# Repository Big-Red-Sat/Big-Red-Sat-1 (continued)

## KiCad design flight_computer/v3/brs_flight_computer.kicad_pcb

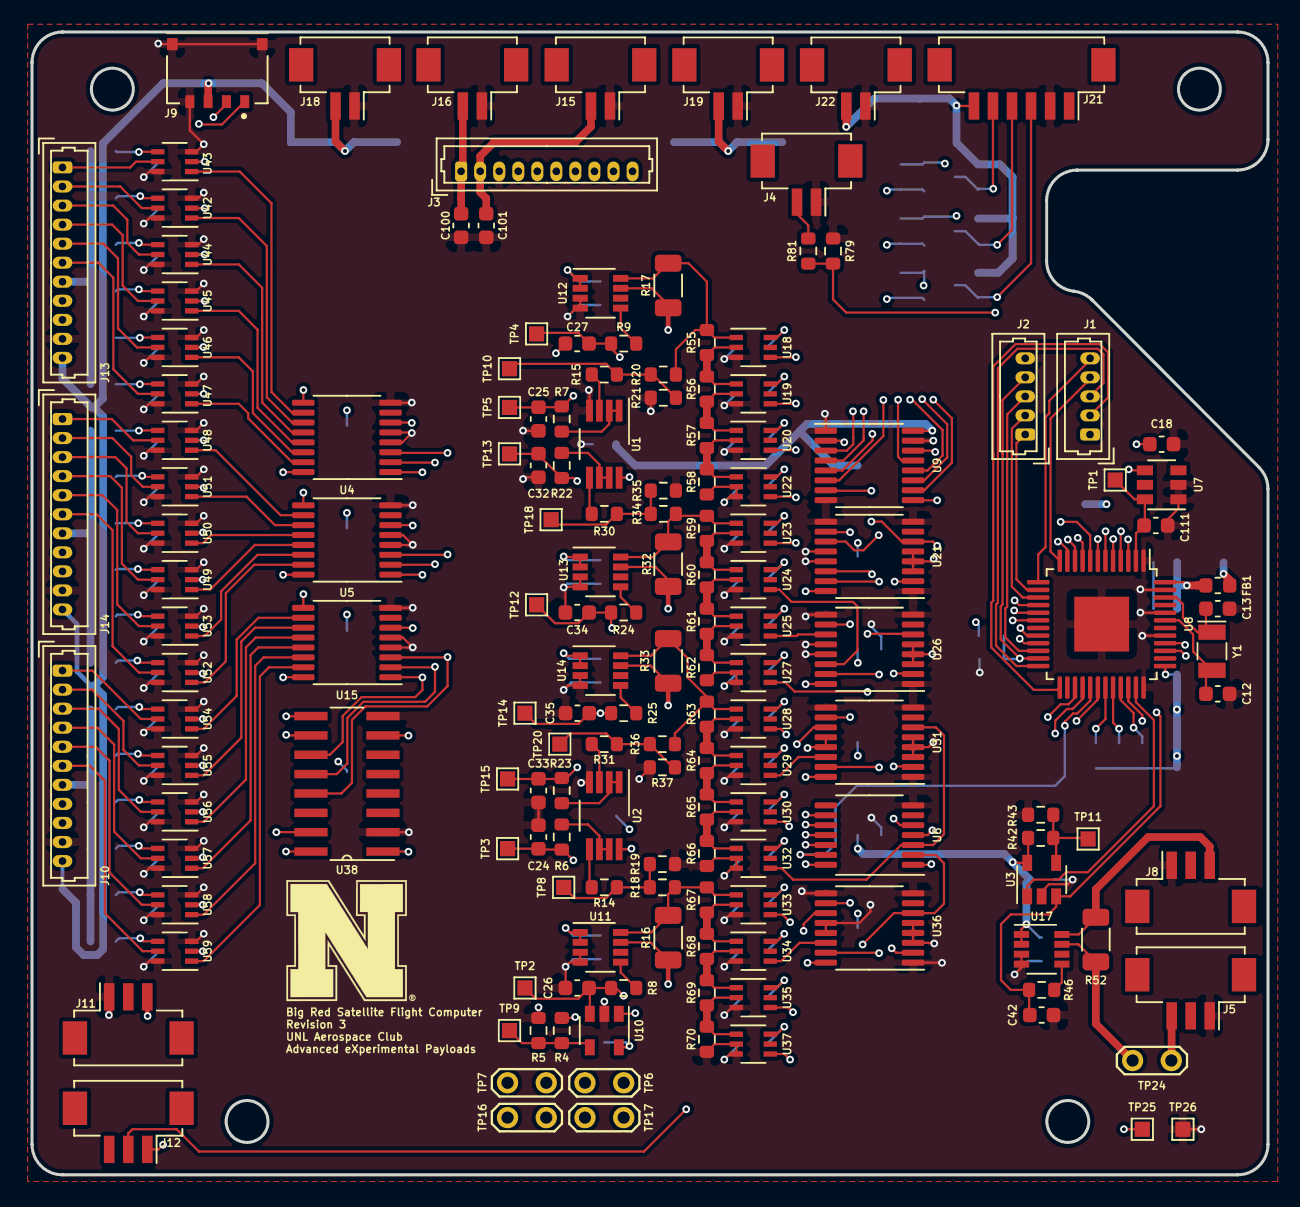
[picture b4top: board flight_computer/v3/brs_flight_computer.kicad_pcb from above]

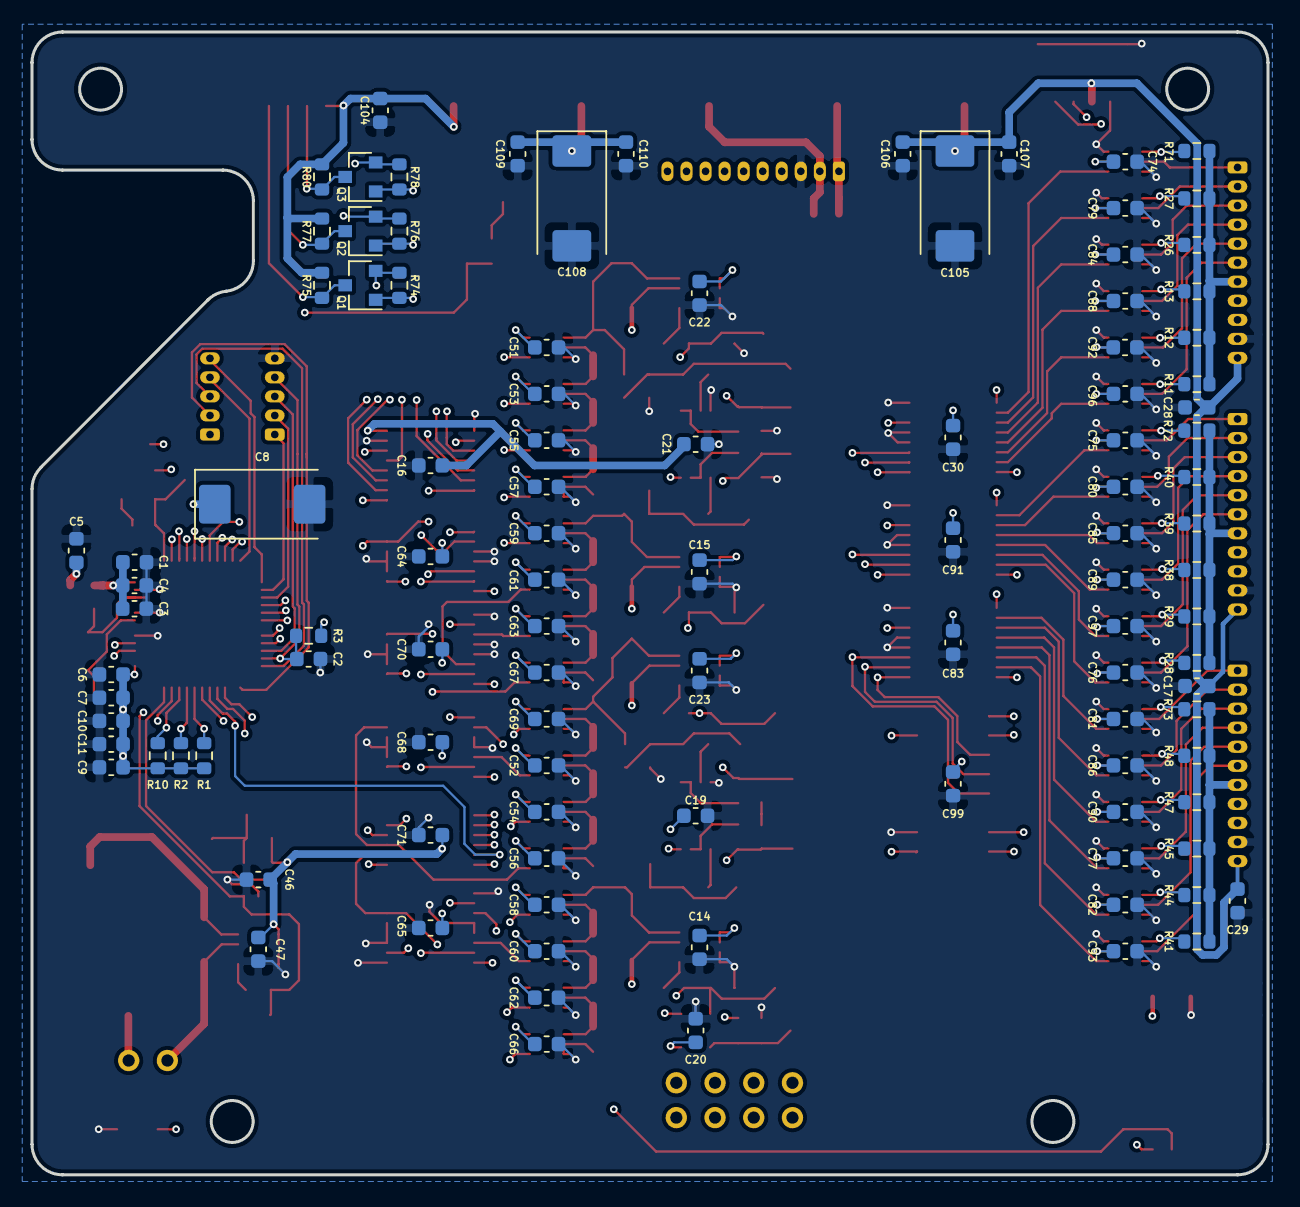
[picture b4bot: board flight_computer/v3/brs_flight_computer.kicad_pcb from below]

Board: 4 copper layers, 81.1 x 75.0 mm, 265 parts (105 on the bottom side), 177 nets.

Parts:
C1, C10, C100, C106, C109: 10u; C_0603_1608Metric
C2, C4, C5, C6, C9, C11, C14, C15, C16, C17, C18, C19, C20, C21, C22, C23, C28, C29, C30, C51, C52, C53, C54, C55, C56, C57, C58, C59, C60, C61, C62, C63, C64, C65, C66, C67, C68, C69, C70, C71, C74, C75, C76, C77, C79, C80, C81, C82, C83, C84, C85, C86, C88, C89, C90, C91, C92, C93, C96, C97, C99, C101, C104, C107, C110, C111: 0.1u; C_0603_1608Metric
C3, C7, C46, C47: 1u; C_0603_1608Metric
C8, C105, C108: 47u; CP_EIA-7343-43_Kemet-X
C12, C13: 10p; C_0603_1608Metric
C24, C25, C26, C27, C32, C33, C34, C35, C42: 10n; C_0603_1608Metric
FB1: Ferrite_Bead_Small; L_0603_1608Metric
J1, J2: Conn_01x05_Male; Molex_PicoBlade_53047-0510_1x05_P1.25mm_Vertical
J3: Conn_01x10_Male; Molex_PicoBlade_53047-1010_1x10_P1.25mm_Vertical
J4: BUSS; Hirose_DF13C_CL535-0402-2-51_1x02-1MP_P1.25mm_Vertical
J5: Panel 3; Hirose_DF13C_CL535-0403-5-51_1x03-1MP_P1.25mm_Vertical
J8: Conn_01x03_Male; Hirose_DF13C_CL535-0403-5-51_1x03-1MP_P1.25mm_Vertical
J9: 0781710004; MOLEX_0781710004
J10: Perovskite 3; Molex_PicoBlade_53047-1110_1x11_P1.25mm_Vertical
J11: GaAs Panel; Hirose_DF13C_CL535-0403-5-51_1x03-1MP_P1.25mm_Vertical
J12: GaAs Temperature; Hirose_DF13C_CL535-0403-5-51_1x03-1MP_P1.25mm_Vertical
J13: Perovskite 1; Molex_PicoBlade_53047-1110_1x11_P1.25mm_Vertical
J14: Perovskite 2; Molex_PicoBlade_53047-1110_1x11_P1.25mm_Vertical
J15, J16, J18, J19, J22: Power; Hirose_DF13C_CL535-0402-2-51_1x02-1MP_P1.25mm_Vertical
J21: EPS Serial; Hirose_DF13C_CL535-0406-3-51_1x06-1MP_P1.25mm_Vertical
Q1, Q2, Q3: BSS138; SOT-23
R1, R2, R10: 4k7; R_0603_1608Metric
R3, R74, R75, R76, R77, R78, R80: 10k; R_0603_1608Metric
R4, R5, R6, R7, R8, R9, R14, R15, R22, R23, R24, R25, R30, R31, R42, R43, R46: 470; R_0603_1608Metric
R11, R12, R13, R26, R27, R28, R29, R38, R39, R40, R41, R44, R45, R47, R48, R71, R72, R73: 400; R_0603_1608Metric
R16, R17, R32, R33, R52: 510m; R_1206_3216Metric
R18, R81: 3M; R_0603_1608Metric
R19, R20, R21, R34, R35, R36, R37, R55, R59, R63, R67, R79: 1M; R_0603_1608Metric
R56, R60, R64, R68: 430; R_0603_1608Metric
R57, R61, R65, R69: 270; R_0603_1608Metric
R58, R62, R66, R70: 120; R_0603_1608Metric
TP1: VREF; TestPoint_Pad_1.0x1.0mm
TP2, TP4, TP11, TP12, TP14: I; TestPoint_Pad_1.0x1.0mm
TP3, TP5, TP13, TP15: V; TestPoint_Pad_1.0x1.0mm
TP6, TP7, TP16, TP17, TP24: Current Test; TestPoint_2Pads_Pitch2.54mm_Drill0.8mm
TP8, TP9, TP10, TP18, TP20: Voltage Test+; TestPoint_Pad_1.0x1.0mm
TP25: 3V3; TestPoint_Pad_1.0x1.0mm
TP26: GND; TestPoint_Pad_1.0x1.0mm
U1, U2: OPA2387; VSSOP-8_3.0x3.0mm_P0.65mm
U3, U10: TLV7031DBV; SOT-23-5
U4, U5, U15: 74HC237; TSSOP-16_4.4x5mm_P0.65mm
U6: 4012; TSSOP-14_4.4x5mm_P0.65mm
U7: LT6654AHS6-3.3; SOT-23-6
U8: MSP430FR5969IRGZR; LQFP-48-1EP_7x7mm_P0.5mm_EP3.6x3.6mm
U9: SN74CBT3253; TSSOP-16_4.4x5mm_P0.65mm
U11, U12, U13, U14, U17: INA190A4IDDFR
U18, U19, U20, U22, U23, U24, U25, U27, U28, U29, U30, U32, U33, U34, U35, U37: ADG841YKSZ-500RL7
U21, U26, U31, U36: CD4516B_PW_16; TSSOP-16_4.4x5mm_P0.65mm
U38: CD4518BM96
U42, U43, U44, U45, U46, U47, U48, U49, U50, U51, U52, U53, U54, U55, U56, U57, U58, U59: ADG839YKSZ-REEL7
Y1: CM8V-T1A; Crystal_SMD_MicroCrystal_CC7V-T1A-2Pin_3.2x1.5mm

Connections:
+3V3: C5.1, C6.1, C7.1, C8.1, C9.2, C10.2, C11.2, C14.1, C16.1, C18.2, C20.1, C21.1, C30.1, C58.1, C60.1, C62.1, C65.1, C66.1, C74.1, C75.1, C76.1, C77.1, C79.1, C80.1, C81.1, C82.1, C83.1, C84.1, C85.1, C86.1, C88.1, C89.1, C90.1, C91.1, C92.1, C93.1, C96.1, C97.1, C99.1, C108.1, C109.1, C110.1, FB1.1, J1.1, J12.1, J19.2, Q1.1, Q2.1, Q3.1, R1.2, R2.2, R3.2, R4.1, R10.2, R74.2, R76.2, R78.2, TP25.1, U2.8, U4.6, U4.16, U5.6, U5.16, U6.12, U7.4, U8.37, U9.16, U10.5, U11.1, U11.2, U15.6, U15.16, U33.6, U34.6, U35.6, U36.16, U37.6, U38.1, U38.7, U38.10, U38.16, U42.2, U43.2, U44.2, U45.2, U46.2, U47.2, U48.2, U49.2, U50.2, U51.2, U52.2, U53.2, U54.2, U55.2, U56.2, U57.2, U58.2, U59.2
+5V: C104.1, J21.6, J22.2, R75.2, R77.2, R80.2
/Curve Tracer/GAAS_LADDER: R16.1, R18.2, R67.2, U11.8, U33.1
/Curve Tracer/GAAS_ON: U8.28, U10.1
/Curve Tracer/GAAS_POS: J11.3, TP6.1
/Curve Tracer/P_1_LADDER: R17.2, R20.2, R55.2, U12.8, U18.1
/Curve Tracer/P_2_LADDER: R32.1, R34.2, R59.2, U13.8, U23.1
/Curve Tracer/P_3_LADDER: R33.2, R36.2, R63.2, U14.8, U28.1
/Curve Tracer/READ_CURRENT: U8.10, U9.7
/Curve Tracer/READ_VOLTAGE: U8.11, U9.9
/Curve Tracer/S0_CT: U8.8, U9.14
/Curve Tracer/S1_CT: U8.9, U9.2
/EPS Connections/BUSY: Q1.2, R74.1, U8.34
/EPS Connections/READ_BUSS: R79.1, R81.1, U8.16
/EPS Connections/RX: Q3.2, R78.1, U8.21
/EPS Connections/TX: Q2.2, R76.1, U8.20
/Ground Switcher/GAAS_TEMP: J12.2, R10.1, U8.33
/Ground Switcher/MUX_CLOCK: U8.30, U38.9
/Ground Switcher/MUX_GOOD: U6.13, U8.29
/Ground Switcher/MUX_RESET: U8.39, U38.15
/Ground Switcher/SCL: J3.4, J9.2, J10.9, J13.9, J14.9, R2.1, U8.32
/Ground Switcher/SDA: J3.5, J9.1, J10.8, J13.8, J14.8, R1.1, U8.31
/Microcontroller/CT_GOOD: U6.1, U8.27
/Microcontroller/LADDER_CLOCK: U8.17, U21.15, U26.15, U31.15, U36.15
/Microcontroller/MAG_INT: J3.6, U8.7
/Microcontroller/NC_V: J3.10, U8.3
/Microcontroller/NO_V: J3.9, U8.4
/Microcontroller/PANEL_3_CURRENT_V: C42.1, R46.1, U3.3, U8.40
/Microcontroller/SET: J3.7, U8.6
/Microcontroller/TRACE_DIR: U8.18, U21.10, U26.10, U31.10, U36.10
/Microcontroller/UNSET: J3.8, U8.5
/Passive ADCS/PANEL_3_CURRENT: U3.1, U8.35
GAAS_CURRENT: C26.1, R8.1, TP2.1, U9.6, U10.3
GAAS_VOLTAGE: C24.1, R6.1, TP3.1, U9.10
GND: C1.2, C2.1, C3.2, C4.2, C5.2, C6.2, C7.2, C8.2, C9.1, C10.1, C11.1, C12.2, C13.1, C14.2, C15.2, C16.2, C17.2, C18.1, C19.2, C20.2, C21.2, C22.2, C23.2, C24.2, C25.2, C26.2, C27.2, C28.2, C29.2, C30.2, C32.2, C33.2, C34.2, C35.2, C42.2, C46.2, C47.2, C51.2, C52.2, C53.2, C54.2, C55.2, C56.2, C57.2, C58.2, C59.2, C60.2, C61.2, C62.2, C63.2, C64.2, C65.2, C66.2, C67.2, C68.2, C69.2, C70.2, C71.2, C74.2, C75.2, C76.2, C77.2, C79.2, C80.2, C81.2, C82.2, C83.2, C84.2, C85.2, C86.2, C88.2, C89.2, C90.2, C91.2, C92.2, C93.2, C96.2, C97.2, C99.2, C100.2, C101.2, C104.2, C105.2, C106.2, C107.2, C108.2, C109.2, C110.2, C111.1, J2.5, J3.3, J4.1, J5.1, J8.1, J9.4, J9.S1, J9.S2, J10.10, J11.1, J13.10, J14.10, J15.1, J16.1, J18.1, J19.1, J21.2, J22.1, R5.2, R19.1, R21.1, R35.1, R37.1, R43.2, R58.1, R62.1, R66.1, R70.1, R79.2, TP26.1, U1.4, U2.4, U3.2, U4.4, U4.5, U4.8, U5.4, U5.5, U5.8, U6.7, U7.1, U7.2, U8.1, U8.36, U8.41, U8.44, U8.47, U8.49, U9.1, U9.8, U9.15, U10.2, U11.3, U11.4, U12.3, U12.4, U13.3, U13.4, U14.3, U14.4, U15.4, U15.5, U15.8, U17.3, U17.4, U18.3, U19.3, U20.3, U21.1, U21.3, U21.4, U21.5, U21.8, U21.9, U21.12, U21.13, U22.2, U22.3, U23.3, U24.3, U25.3, U26.1, U26.3, U26.4, U26.5, U26.8, U26.9, U26.12, U26.13, U27.2, U27.3, U28.3, U29.3, U30.3, U31.1, U31.3, U31.4, U31.5, U31.8, U31.9, U31.12, U31.13, U32.2, U32.3, U33.3, U34.3, U35.3, U36.1, U36.3, U36.4, U36.5, U36.8, U36.9, U36.12, U36.13, U37.2, U37.3, U38.2, U38.8, U42.3, U42.6, U43.3, U43.6, U44.3, U44.6, U45.3, U45.6, U46.3, U46.6, U47.3, U47.6, U48.3, U48.6, U49.3, U49.6, U50.3, U50.6, U51.3, U51.6, U52.3, U52.6, U53.3, U53.6, U54.3, U54.6, U55.3, U55.6, U56.3, U56.6, U57.3, U57.6, U58.3, U58.6, U59.3, U59.6
unnamed: C12.1, U8.43, Y1.2
unnamed: C13.2, U8.46, Y1.1
unnamed: C111.2, TP1.1, U7.6, U8.2
unnamed: J4.2, R81.2
unnamed: J5.3, TP24.1
unnamed: J8.3, R52.1, U17.8
unnamed: J21.3, Q1.3, R75.1
unnamed: J21.4, Q2.3, R77.1
unnamed: J21.5, Q3.3, R80.1
unnamed: R4.2, R5.1, TP9.1, U10.4
unnamed: R6.2, U2.6, U2.7
unnamed: R7.2, U1.1, U1.2
unnamed: R8.2, U11.5
unnamed: R9.2, U12.5
unnamed: R11.2, U47.4
unnamed: R12.2, U46.4
unnamed: R13.2, U45.4
unnamed: R14.1, U2.5
unnamed: R14.2, R18.1, R19.2, TP8.1
unnamed: R15.1, U1.3
unnamed: R15.2, R20.1, R21.2, TP10.1
unnamed: R16.2, TP6.2, U11.7
unnamed: R17.1, TP7.2, U12.7
unnamed: R22.2, U1.6, U1.7
unnamed: R23.2, U2.1, U2.2
unnamed: R24.2, U13.5
unnamed: R25.2, U14.5
unnamed: R26.2, U44.4
unnamed: R27.2, U42.4
unnamed: R28.2, U52.4
unnamed: R29.2, U53.4
unnamed: R30.1, U1.5
unnamed: R30.2, R34.1, R35.2, TP18.1
unnamed: R31.1, U2.3
unnamed: R31.2, R36.1, R37.2, TP20.1
unnamed: R32.2, TP16.2, U13.7
unnamed: R33.1, TP17.2, U14.7
unnamed: R38.2, U49.4
unnamed: R39.2, U50.4
unnamed: R40.2, U51.4
unnamed: R41.2, U59.4
unnamed: R42.2, R43.1, TP11.1, U3.4
unnamed: R44.2, U58.4
unnamed: R45.2, U57.4
unnamed: R46.2, U17.5
unnamed: R47.2, U56.4
unnamed: R48.2, U55.4
unnamed: R52.2, TP24.2, U17.7
unnamed: R55.1, R56.2, U18.2, U19.1
unnamed: R56.1, R57.2, U19.2, U20.1
unnamed: R57.1, R58.2, U20.2, U22.1
unnamed: R59.1, R60.2, U23.2, U24.1
unnamed: R60.1, R61.2, U24.2, U25.1
unnamed: R61.1, R62.2, U25.2, U27.1
unnamed: R63.1, R64.2, U28.2, U29.1
unnamed: R64.1, R65.2, U29.2, U30.1
unnamed: R65.1, R66.2, U30.2, U32.1
unnamed: R67.1, R68.2, U33.2, U34.1
unnamed: R68.1, R69.2, U34.2, U35.1
unnamed: R69.1, R70.2, U35.2, U37.1
unnamed: R71.2, U43.4
unnamed: R72.2, U48.4
unnamed: R73.2, U54.4
unnamed: U4.9, U6.9
unnamed: U4.10, U43.1
unnamed: U4.11, U42.1
unnamed: U4.12, U44.1
unnamed: U4.13, U45.1
unnamed: U4.14, U46.1
unnamed: U4.15, U47.1
unnamed: U5.9, U6.10
unnamed: U5.11, U51.1
unnamed: U5.12, U50.1
unnamed: U5.14, U53.1
unnamed: U5.15, U52.1
unnamed: U4.1, U5.1, U15.1, U38.11
unnamed: U4.2, U5.2, U15.2, U38.12
unnamed: U4.3, U5.3, U15.3, U38.13
unnamed: U6.11, U15.9
unnamed: U15.10, U54.1
unnamed: U15.11, U55.1
unnamed: U15.12, U56.1
unnamed: U15.13, U57.1
unnamed: U15.14, U58.1
unnamed: U15.15, U59.1
unnamed: U18.4, U21.2
unnamed: U19.4, U21.14
unnamed: U20.4, U21.11
unnamed: U6.5, U21.6, U22.4
unnamed: U23.4, U26.2
unnamed: U24.4, U26.14
unnamed: U25.4, U26.11
unnamed: U6.4, U26.6, U27.4
unnamed: U28.4, U31.2
unnamed: U29.4, U31.14
unnamed: U30.4, U31.11
unnamed: U6.3, U31.6, U32.4
unnamed: U33.4, U36.2
unnamed: U34.4, U36.14
unnamed: U35.4, U36.11
unnamed: U6.2, U36.6, U37.4
unnamed: U5.10, U48.1
unnamed: U5.13, U49.1
P1_CP: J13.7, R11.1, R12.1, R13.1, R26.1, R27.1, R71.1, TP7.1
P1_P1: J13.6, U47.5
P1_P2: J13.5, U46.5
P1_P3: J13.4, U45.5
P1_P4: J13.1, U43.5
P1_P5: J13.2, U42.5
P1_P6: J13.3, U44.5
P2_CP: J14.7, R28.1, R29.1, R38.1, R39.1, R40.1, R72.1, TP16.1
P2_P1: J14.6, U52.5
P2_P2: J14.5, U53.5
P2_P3: J14.4, U49.5
P2_P4: J14.1, U48.5
P2_P5: J14.2, U51.5
P2_P6: J14.3, U50.5
P3_CP: J10.7, R41.1, R44.1, R45.1, R47.1, R48.1, R73.1, TP17.1
P3_P1: J10.6, U59.5
P3_P2: J10.5, U58.5
P3_P3: J10.4, U57.5
P3_P4: J10.1, U54.5
P3_P5: J10.2, U55.5
P3_P6: J10.3, U56.5
PAYLOAD_RST: C2.2, J2.4, R3.1, U8.23
P_1_CURRENT: C27.1, R9.1, TP4.1, U9.3
P_1_VOLTAGE: C25.1, R7.1, TP5.1, U9.13
P_2_CURRENT: C34.1, R24.1, TP12.1, U9.4
P_2_VOLTAGE: C32.1, R22.1, TP13.1, U9.12
P_3_CURRENT: C35.1, R25.1, TP14.1, U9.5
P_3_VOLTAGE: C33.1, R23.1, TP15.1, U9.11
RX_IN: J1.2, U8.25
TCK: J2.2, U8.15
TDI: J1.5, U8.13
TDO: J1.4, U8.12
TEST: J2.3, U8.22
TMS: J2.1, U8.14
TX_OUT: J1.3, U8.24
VAA: C1.1, C3.1, C4.1, FB1.2, U8.48
VBUS: C15.1, C17.1, C19.1, C22.1, C23.1, C28.1, C29.1, C46.1, C47.1, C51.1, C52.1, C53.1, C54.1, C55.1, C56.1, C57.1, C59.1, C61.1, C63.1, C64.1, C67.1, C68.1, C69.1, C70.1, C71.1, C105.1, C106.1, C107.1, J9.3, J10.11, J13.11, J14.11, J18.2, R42.1, U1.8, U3.5, U6.14, U12.1, U12.2, U13.1, U13.2, U14.1, U14.2, U17.1, U17.2, U18.6, U19.6, U20.6, U21.16, U22.6, U23.6, U24.6, U25.6, U26.16, U27.6, U28.6, U29.6, U30.6, U31.16, U32.6
VDDF: C100.1, J3.1, J16.2
VPP: C101.1, J3.2, J15.2

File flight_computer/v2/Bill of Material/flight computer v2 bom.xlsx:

Ref | Quantity | Value | Footprint | Rating | Vendor
C1, C10, C100, C106, C109, | 5 | 10u | Capacitor_SMD:C_0603_1608Metric | AEC-Q200 | https://www.digikey.com/en/products/detail/kyocera-avx/KAM15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
C2, C4, C5, C6, C9, C11, C14, C15, C16, C17, C18, C19, C20, C21, C22, C23, C28,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 | 66 | 0.1u | Capacitor_SMD:C_0603_1608Metric | COTS | https://www.digikey.com/en/products/detail/kemet/C0603T104K5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
C3, C7, C46, C47, C48, | 5 | 1u | Capacitor_SMD:C_0603_1608Metric | AEC-Q200 | https://www.digikey.com/en/products/detail/tdk-corporation/C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
C8, C105, C108, | 3 | 47u | Capacitor_Tantalum_SMD:CP_EIA-7343-43_Kemet-X | COTS | https://www.digikey.com/en/products/detail/kemet/T541X227M01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
C12, C13, | 2 | 10p | Capacitor_SMD:C_0603_1608Metric | COTS | https://www.digikey.com/en/products/detail/kemet/C0603T100J5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
C24, C25, C26, C27, C32, C33, C34, C35, C42, | 9 | 10n | Capacitor_SMD:C_0603_1608Metric | COTS | https://www.digikey.com/en/products/detail/kemet/C0603T103K5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
FB1, | 1 | Ferrite_Bead_Small | Inductor_SMD:L_0603_1608Metric | AEC-Q200 | https://www.digikey.com/en/products/detail/tdk-corporation/M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
R1, R2, | 2 | 4k7 | Resistor_SMD:R_0603_1608Metric | AEC-Q200 | https://www.digikey.com/en/products/detail/vishay-dale/TNPW0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
R3, R71, R72, R73, R74, R75, R76, R77, R78, R80, | 10 | 10k | Resistor_SMD:R_0603_1608Metric | "Military" | https://www.digikey.com/en/products/detail/vishay-dale/TNPW0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
R4, R5, R6, R7, R8, R9, R14, R15, R22, R23, R24, R25, R30, R31, R42, R43, R46, | 17 | 470 | Resistor_SMD:R_0603_1608Metric | AEC-Q200 | https://www.digikey.com/en/products/detail/susumu/RG1608P-47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
R16, R17, R32, R33, R52, | 5 | 510m | Resistor_SMD:R_1206_3216Metric | AEC-Q200 | https://www.digikey.com/en/products/detail/koa-speer-electro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
R18, R19, R20, R21, R34, R35, R36, R37, | 8 | 10M | Resistor_SMD:R_0603_1608Metric | AEC-Q200 | https://www.digikey.com/en/products/detail/vishay-dale/CRCW0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
R55, R59, R63, R67, | 4 | 120 | Resistor_SMD:R_0603_1608Metric | AEC-Q200 | https://www.digikey.com/en/products/detail/susumu/RG1608N-12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
R56, R60, R64, R68, | 4 | 270 | Resistor_SMD:R_0603_1608Metric | AEC-Q200 | https://www.digikey.com/en/products/detail/susumu/RG1608N-27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
R57, R61, R65, R69, | 4 | 430 | Resistor_SMD:R_0603_1608Metric | AEC-Q200 | https://www.digikey.com/en/products/detail/susumu/RG1608N-43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
R58, R62, R66, R70, R79, | 5 | 1M | Resistor_SMD:R_0603_1608Metric | AEC-Q200 | https://www.digikey.com/en/products/detail/rohm-semiconducto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
R81, | 1 | 3M | Resistor_SMD:R_0603_1608Metric | AEC-Q200 | https://www.digikey.com/en/products/detail/rohm-semiconducto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
Y1, | 1 | CM8V-T1A | CM8V-T1A-32:XTAL_CM8V-T1A-32.768KHZ-7PF-20PPM-TA-QC | AEC-Q200 | https://www.digikey.com/en/products/detail/jauch-quartz/Q-0-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
J5, | 1 | Panel 3 Input | Connector_Hirose:Hirose_DF13C_CL535-0403-5-51_1x03-1MP_P1.25mm_Vertical |  | https://www.digikey.com/en/products/detail/hirose-electric-c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
J8, | 1 | Panel 3 Output | Connector_Hirose:Hirose_DF13C_CL535-0403-5-51_1x03-1MP_P1.25mm_Vertical |  | https://www.digikey.com/en/products/detail/hirose-electric-c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
J9, | 1 | Sun Vector Sensor | 0781710004:MOLEX_0781710004 |  | https://www.digikey.com/en/products/detail/molex/0781710004/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
J11, | 1 | GaAs Panel | Connector_Hirose:Hirose_DF13C_CL535-0403-5-51_1x03-1MP_P1.25mm_Vertical |  | https://www.digikey.com/en/products/detail/hirose-electric-c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
J12, | 1 | GaAs Temperature | Connector_Hirose:Hirose_DF13C_CL535-0403-5-51_1x03-1MP_P1.25mm_Vertical |  | https://www.digikey.com/en/products/detail/hirose-electric-c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
J15, J16, J18, J19, J22, | 5 | Power | Connector_Hirose:Hirose_DF13C_CL535-0402-2-51_1x02-1MP_P1.25mm_Vertical |  | https://www.digikey.com/en/products/detail/hirose-electric-c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
J20, | 1 | BUSS+ | Connector_Hirose:Hirose_DF13C_CL535-0404-8-51_1x04-1MP_P1.25mm_Vertical |  | https://www.digikey.com/en/products/detail/hirose-electric-c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
J21, | 1 | EPS Serial | Connector_Hirose:Hirose_DF13C_CL535-0406-3-51_1x06-1MP_P1.25mm_Vertical |  | https://www.digikey.com/en/products/detail/hirose-electric-c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
Q1, Q2, Q3, | 3 | BSS138 | Package_TO_SOT_SMD:SOT-23 |  | https://www.digikey.com/en/products/detail/anbon-semiconduct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
U1, U2, | 2 | OPA2387 | Package_SO:VSSOP-8_3.0x3.0mm_P0.65mm |  | https://www.digikey.com/en/products/detail/texas-instruments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
U3, U10, | 2 | TLV7031DBV | Package_TO_SOT_SMD:SOT-23-5 |  | https://www.digikey.com/en/products/detail/texas-instruments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
U6, | 1 | CD4012BPWR | Package_SO:TSSOP-14_4.4x5mm_P0.65mm |  | https://www.digikey.com/en/products/detail/texas-instruments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
U7, | 1 | LT6654AHS6-3.3 | Package_TO_SOT_SMD:SOT-23-6 |  | https://www.digikey.com/en/products/detail/analog-devices-in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
U8, | 1 | MSP430FR5969IRGZR | MSP430FR5969IRGZR:QFN50P700X700X100-49N |  | https://www.digikey.com/en/products/detail/texas-instruments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
U9, | 1 | 74CBTLV3253PW,118 | Package_SO:TSSOP-16_4.4x5mm_P0.65mm |  | https://www.digikey.com/en/products/detail/nexperia-usa-inc/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
U11, U12, U13, U14, U17, | 5 | INA190A4IDDFR | ul_INA190A4IDDFR:INA190A4IDDFR |  | https://www.digikey.com/en/products/detail/texas-instruments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
U18, U19, U20, U22, U23, U24, U25, U27, U28, U29, U30, U32, U33, U34, U35, U37, | 16 | ADG841YKSZ-500RL7 | ul_ADG841YKSZ-500RL7:ADG841YKSZ-500RL7 |  | https://www.digikey.com/en/products/detail/analog-devices-in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
U21, U26, U31, U36, | 4 | CD4516B_PW_16 | Package_SO:TSSOP-16_4.4x5mm_P0.65mm |  | https://www.digikey.com/en/products/detail/texas-instruments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
U38, | 1 | CD4518BM96 | ul_CD4518BM96:CD4518BM96 |  | https://www.digikey.com/en/products/detail/texas-instruments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
U39, | 1 | 74AHC1G08 | Package_TO_SOT_SMD:SOT-23-5 |  | https://www.digikey.com/en/products/detail/texas-instruments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
U40, U41, | 2 | CD4514BM | ul_CD4514BM:CD4514BM |  | https://www.digikey.com/en/products/detail/texas-instruments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
U42, U43, U44, U45, U46, U47, U48, U49, U50, U51, U52, U53, U54, U55, U56, U57,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 | 18 | ADG839YKSZ-REEL7 | ul_ADG839YKSZ-REEL7:ADG839YKSZ-REEL7 |  | https://www.digikey.com/en/products/detail/analog-devices-in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

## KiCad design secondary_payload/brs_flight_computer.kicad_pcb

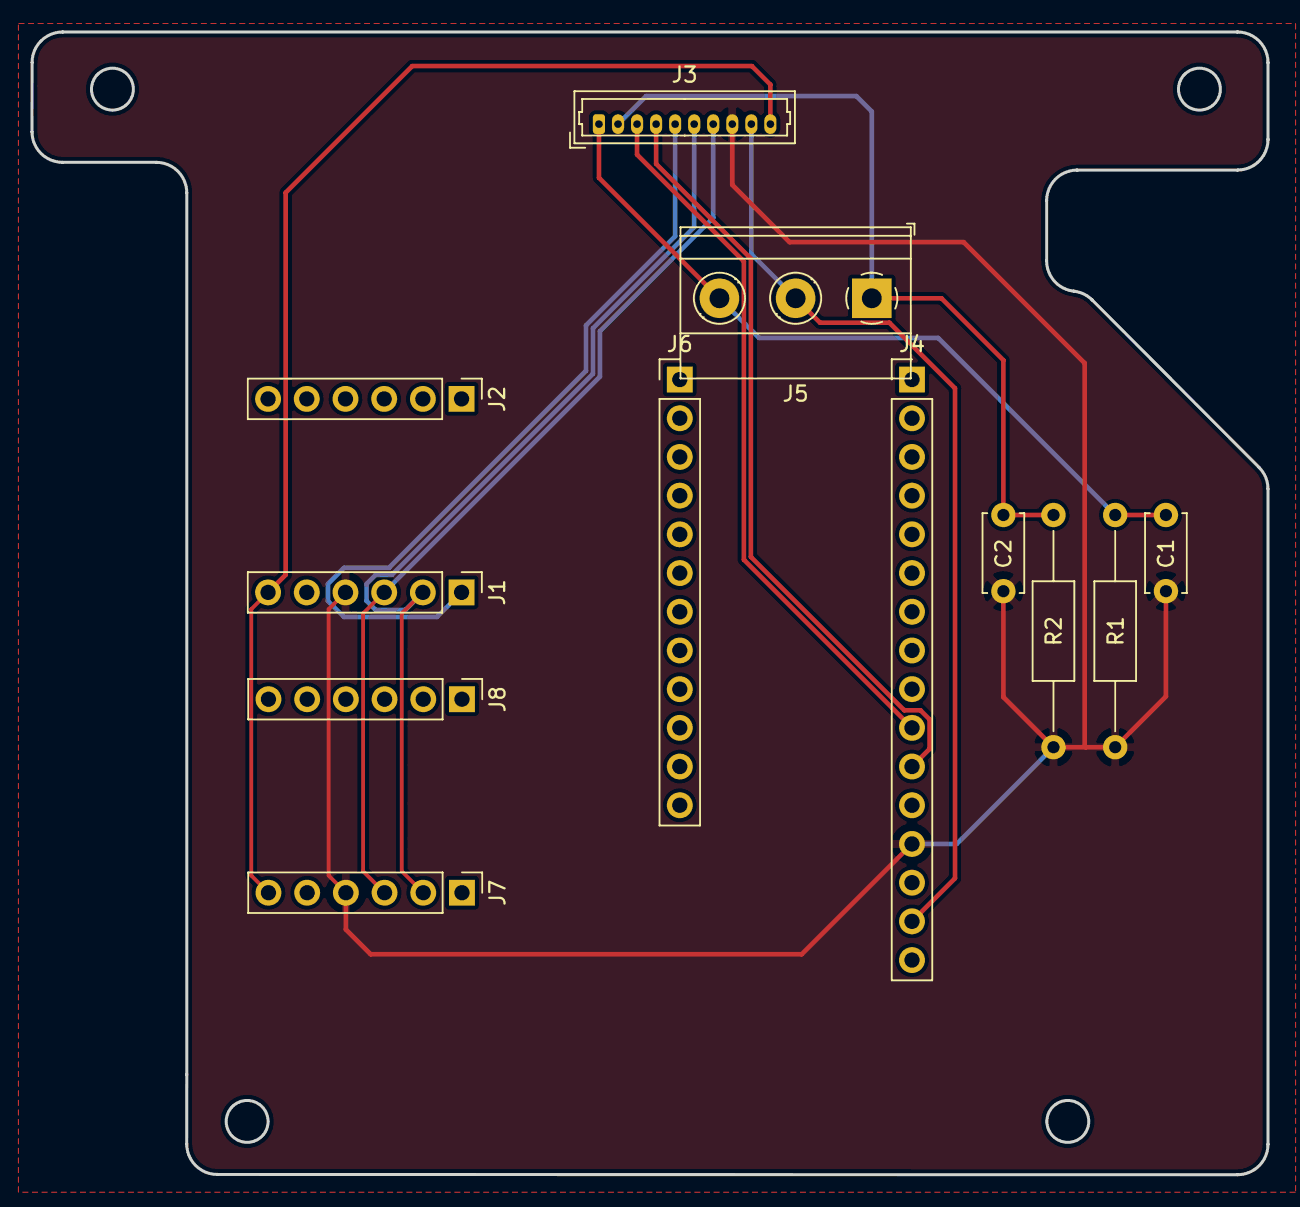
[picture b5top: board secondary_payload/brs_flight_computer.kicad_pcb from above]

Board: 2 copper layers, 81.1 x 75.0 mm, 12 parts (0 on the bottom side), 10 nets.

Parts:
C1, C2: C; C_Disc_D5.0mm_W2.5mm_P5.00mm
J1, J2, J7, J8: Conn_01x06_Male; PinHeader_1x06_P2.54mm_Vertical
J3: Conn_01x10_Male; Molex_PicoBlade_53047-1010_1x10_P1.25mm_Vertical
J4: Conn_01x16_Male; PinHeader_1x16_P2.54mm_Vertical
J5: Conn_01x03_Male; TerminalBlock_Phoenix_MKDS-1,5-3_1x03_P5.00mm_Horizontal
J6: Conn_01x12_Male; PinHeader_1x12_P2.54mm_Vertical
R1, R2: R; R_Axial_DIN0207_L6.3mm_D2.5mm_P15.24mm_Horizontal

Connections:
/MAG_INT: J1.1, J3.5
/NC_V: C1.1, J3.1, J5.3, R1.1
/NO_V: C2.1, J3.2, J5.1, R2.1
/SCL: J1.3, J3.7, J7.3
/SDA: J1.2, J3.6, J7.2
/SET: J3.4, J4.11
/UNSET: J3.3, J4.10
GND: C1.2, C2.2, J1.4, J3.8, J4.13, J7.4, R1.2, R2.2
VDDF: J1.6, J3.10, J7.6
VPP: J3.9, J4.15, J5.2

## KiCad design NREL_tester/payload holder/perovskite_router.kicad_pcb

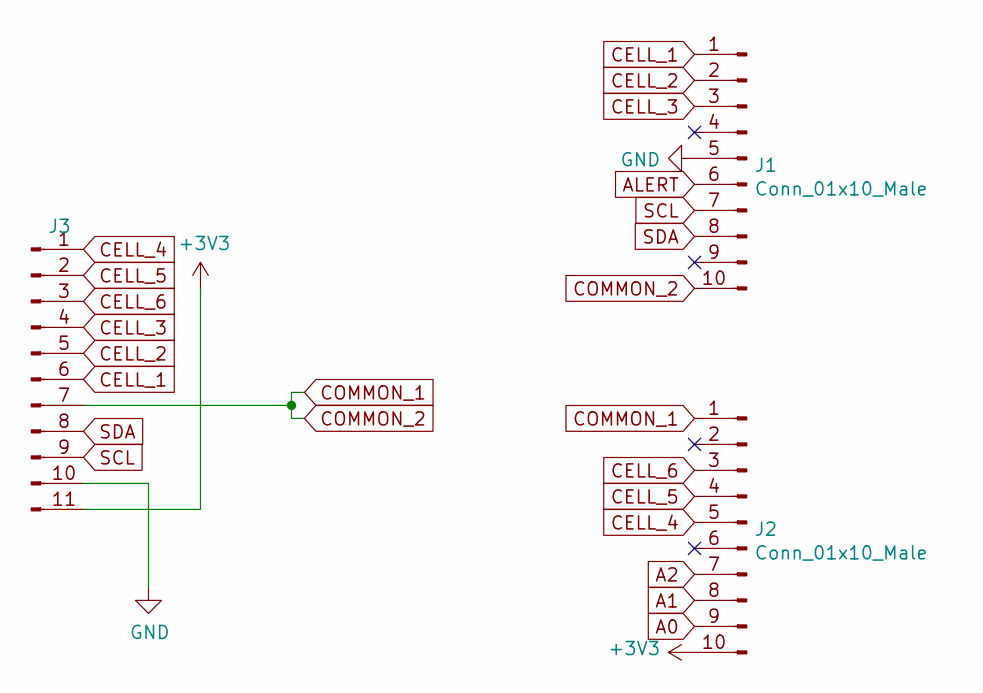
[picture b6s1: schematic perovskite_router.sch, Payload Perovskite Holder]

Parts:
J1, J2: Conn_01x10_Male; PinHeader_1x10_P2.54mm_Vertical
J3: Conn_01x11_Male; PinHeader_1x11_P1.27mm_Vertical

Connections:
+3V3: J2.10, J3.11
A0: J2.9
A1: J2.8
A2: J2.7
ALERT: J1.6
CELL_1: J1.1, J3.6
CELL_2: J1.2, J3.5
CELL_3: J1.3, J3.4
CELL_4: J2.5, J3.1
CELL_5: J2.4, J3.2
CELL_6: J2.3, J3.3
COMMON_1: J1.10, J2.1, J3.7
GND: J1.5, J3.10
SCL: J1.7, J3.9
SDA: J1.8, J3.8

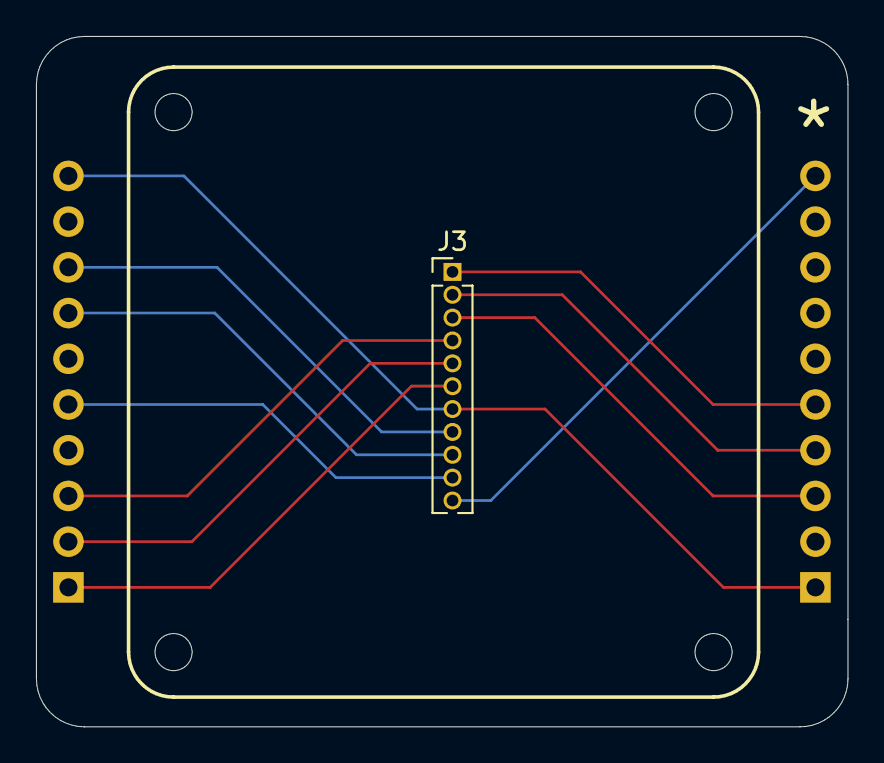
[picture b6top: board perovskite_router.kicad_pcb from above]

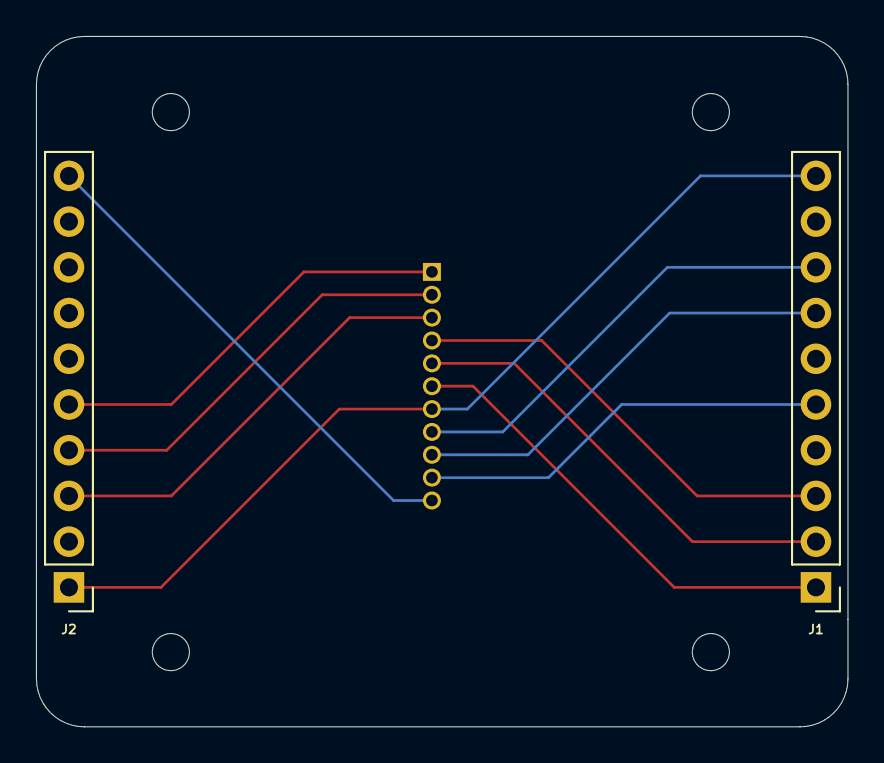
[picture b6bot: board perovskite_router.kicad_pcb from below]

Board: 2 copper layers, 45.1 x 38.4 mm, 3 parts (2 on the bottom side), 11 nets.

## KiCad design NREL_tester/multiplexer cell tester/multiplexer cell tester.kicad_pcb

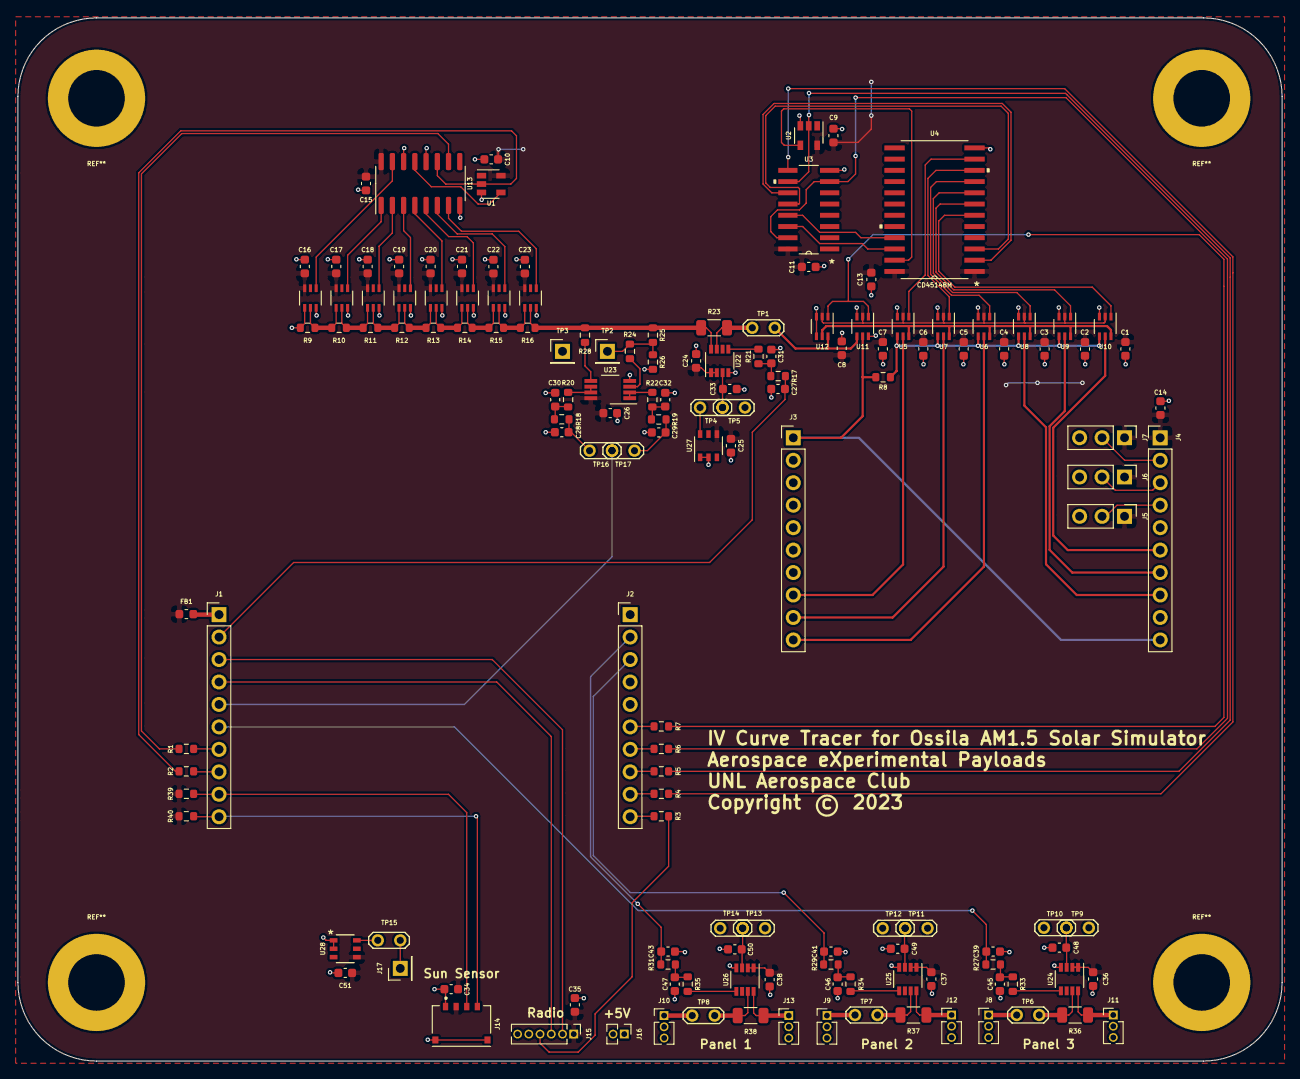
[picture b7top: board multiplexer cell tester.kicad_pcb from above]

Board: 2 copper layers, 143.0 x 118.0 mm, 148 parts (0 on the bottom side), 101 nets.

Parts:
C1, C2, C3, C4, C5, C6, C7, C8, C9, C10, C11, C13, C14, C15, C16, C17, C18, C19, C20, C21, C22, C23, C24, C26, C51: 0.1u; C_0603_1608Metric
C25, C33, C34, C35, C36, C37, C38, C48, C49, C50: 1u; C_0603_1608Metric
C27, C28, C29, C39, C41, C43: 10n; C_0603_1608Metric
C30, C31, C32, C45, C46, C47: 10u; C_0603_1608Metric
FB1: Ferrite_Bead; L_0603_1608Metric
J1, J2, J3, J4: Conn_01x10_Female; PinHeader_1x10_P2.54mm_Vertical
J5: A2 Select; PinHeader_1x03_P2.54mm_Vertical
J6: A1 Select; PinHeader_1x03_P2.54mm_Vertical
J7: A0 Select; PinHeader_1x03_P2.54mm_Vertical
J8: Panel 1; PinHeader_1x03_P1.27mm_Vertical
J9: Panel 2; PinHeader_1x03_P1.27mm_Vertical
J10: Panel 3; PinHeader_1x03_P1.27mm_Vertical
J11, J12, J13: Conn_01x03_Male; PinHeader_1x03_P1.27mm_Vertical
J14: 0781710004; MOLEX_0781710004
J15: Radio; PinHeader_1x06_P1.27mm_Vertical
J16: Power; PinHeader_1x02_P1.27mm_Vertical
J17: Conn_01x01_Male; PinHeader_1x01_P2.54mm_Vertical
R1, R2, R3, R4, R5, R6, R7, R8: 100; R_0603_1608Metric
R9: 50; R_0603_1608Metric
R10: 250; R_0603_1608Metric
R11: 500; R_0603_1608Metric
R12: 1000; R_0603_1608Metric
R13: 2000; R_0603_1608Metric
R14: 4000; R_0603_1608Metric
R15: 8000; R_0603_1608Metric
R16: 16000; R_0603_1608Metric
R17, R18, R19, R24, R27, R28, R29, R31: 470; R_0603_1608Metric
R20, R21, R22, R33, R34, R35: 10k; R_0603_1608Metric
R23, R36, R37, R38: 510m; R_1206_3216Metric
R25, R26: 10M; R_0603_1608Metric
R39, R40: 4k7; R_0603_1608Metric
TP1, TP4, TP5, TP6, TP7, TP8, TP9, TP10, TP11, TP12, TP13, TP14, TP15, TP16, TP17: Current Test; TestPoint_2Pads_Pitch2.54mm_Drill0.8mm
TP2: Voltage Test+; PinHeader_1x01_P2.54mm_Vertical
TP3: Voltage Test-; PinHeader_1x01_P2.54mm_Vertical
U1, U2: SN74LVC1G14DRL; SOT-23-5
U3: CD4518BM96
U4: CD4514BM
U5, U6, U7, U8, U9, U10, U11, U12: ADG839YKSZ-REEL7
U13: 74HC590; SOIC-16_3.9x9.9mm_P1.27mm
U14, U15, U16, U17, U18, U19, U20, U21: ADG841YKSZ-500RL7
U22, U24, U25, U26: INA190A4IDDFR
U23: OPA2387; VSSOP-8_3.0x3.0mm_P0.65mm
U27: LT6654AMPS6-1.25; LT6654AMPS6-1.25-TRMPBF
U28: LT6654AHS6-3.3; LT6654AHS6-3.3-TRMPBF

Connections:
10-19_CLOCK: R4.2, U3.9
+3V3: C1.1, C2.1, C3.1, C4.1, C5.1, C6.1, C7.1, C8.1, C9.1, C10.1, C11.1, C13.1, C14.1, C15.1, C16.1, C17.1, C18.1, C19.1, C20.1, C21.1, C22.1, C23.1, C24.1, C25.1, C26.1, C34.1, C35.1, C36.1, C37.1, C38.1, C51.1, FB1.1, J4.1, J5.1, J6.1, J7.1, J14.2, J15.1, R39.2, R40.2, U1.5, U2.5, U3.16, U4.1, U4.24, U5.2, U6.2, U7.2, U8.2, U9.2, U10.2, U11.2, U12.2, U13.16, U14.6, U15.6, U16.6, U17.6, U18.6, U19.6, U20.6, U21.6, U22.1, U22.2, U23.8, U24.1, U24.2, U25.1, U25.2, U26.1, U26.2, U27.4, U28.4
/Curve Tracer/LADDER_VOLTAGE: R16.1, R23.1, R25.2, R28.2, U21.2, U22.8
/Curve Tracer/PANEL_VOLTAGE: TP1.1, U11.4, U12.6
/Resistor Ladder/LADDER_LATCH: U1.4, U13.13
A0: J4.2, J7.2
A1: J4.3, J6.2
A2: J4.4, J5.2
BUSY: J15.4, R3.2
ENABLE_PANEL_SWITCH: R5.1, U2.2, U3.10
GND: C1.2, C2.2, C3.2, C4.2, C5.2, C6.2, C7.2, C8.2, C9.2, C10.2, C11.2, C13.2, C14.2, C15.2, C16.2, C17.2, C18.2, C19.2, C20.2, C21.2, C22.2, C23.2, C24.2, C25.2, C26.2, C27.2, C28.2, C29.2, C30.2, C31.2, C32.2, C33.2, C34.2, C35.2, C36.2, C37.2, C38.2, C39.2, C41.2, C43.2, C45.2, C46.2, C47.2, C48.2, C49.2, C50.2, C51.2, J2.1, J3.6, J5.3, J6.3, J7.3, J8.3, J9.3, J10.3, J11.3, J12.3, J13.3, J14.1, J14.S1, J14.S2, J15.5, J16.2, R9.2, R26.1, TP3.1, TP5.2, TP10.2, TP12.2, TP14.2, U1.3, U2.3, U3.8, U4.12, U5.3, U6.3, U7.3, U8.3, U9.3, U10.3, U11.3, U11.6, U12.3, U12.4, U13.8, U13.12, U13.14, U14.1, U14.3, U15.3, U16.3, U17.3, U18.3, U19.3, U20.3, U21.3, U22.4, U23.4, U24.4, U25.4, U26.4, U27.1, U27.2, U28.1, U28.2
LADDER_CLOCK: R2.2, U1.2, U13.11
unnamed: C28.1, R18.1, TP16.1
unnamed: C29.1, R19.1, TP17.1
unnamed: C30.1, R18.2, R20.1
unnamed: C31.1, R17.2, R21.1
unnamed: C32.1, R19.2, R22.1
unnamed: C33.1, TP4.1, TP5.1, U22.3
unnamed: C45.1, R27.2, R33.1
unnamed: C46.1, R29.2, R34.1
unnamed: C47.1, R31.2, R35.1
unnamed: C48.1, TP9.1, TP10.1, U24.3
unnamed: C49.1, TP11.1, TP12.1, U25.3
unnamed: C50.1, TP13.1, TP14.1, U26.3
unnamed: FB1.2, J1.1
unnamed: J1.7, R1.1
unnamed: J1.8, R2.1
unnamed: J2.6, R7.2
unnamed: J2.7, R6.2
unnamed: J2.8, R5.2
unnamed: J2.9, R4.1
unnamed: J2.10, R3.1
unnamed: J3.1, J4.10, R8.1, U11.5
unnamed: J3.8, U5.5
unnamed: J3.9, U7.5
unnamed: J3.10, U6.5
unnamed: J4.6, U10.5
unnamed: J4.7, U9.5
unnamed: J4.8, U8.5
unnamed: J8.1, TP6.1
unnamed: J9.1, TP7.1
unnamed: J10.1, TP8.1
unnamed: J11.1, R36.1, U24.8
unnamed: J12.1, R37.1, U25.8
unnamed: J13.1, R38.1, U26.8
unnamed: J17.1, TP15.2
unnamed: R8.2, U5.4, U6.4, U7.4, U8.4, U9.4, U10.4
unnamed: R10.1, R11.2, U15.2, U16.1
unnamed: R9.1, R10.2, U14.2, U15.1
unnamed: R11.1, R12.2, U16.2, U17.1
unnamed: R12.1, R13.2, U17.2, U18.1
unnamed: R13.1, R14.2, U18.2, U19.1
unnamed: R14.1, R15.2, U19.2, U20.1
unnamed: R15.1, R16.2, U20.2, U21.1
unnamed: R20.2, U23.6, U23.7
unnamed: R21.2, U22.5
unnamed: R22.2, U23.1, U23.2
unnamed: R23.2, TP1.2, U22.7
unnamed: R24.1, U23.3
unnamed: R24.2, R25.1, R26.2, TP2.1
unnamed: R28.1, U23.5
unnamed: R33.2, U24.5
unnamed: R34.2, U25.5
unnamed: R35.2, U26.5
unnamed: R36.2, TP6.2, U24.7
unnamed: R37.2, TP7.2, U25.7
unnamed: R38.2, TP8.2, U26.7
unnamed: TP4.2, U27.6
unnamed: TP15.1, U28.6
unnamed: U2.4, U4.23
unnamed: U3.11, U4.2
unnamed: U3.12, U4.3
unnamed: U3.13, U4.21
unnamed: U3.14, U4.22
unnamed: U4.7, U9.1
unnamed: U4.8, U8.1
unnamed: U4.9, U6.1
unnamed: U4.10, U7.1
unnamed: U4.11, U5.1
unnamed: U4.6, U10.1
unnamed: U5.6, U6.6, U7.6, U8.6, U9.6, U10.6, U12.5
unnamed: U13.1, U15.4
unnamed: U13.2, U16.4
unnamed: U13.3, U17.4
unnamed: U13.4, U18.4
unnamed: U13.5, U19.4
unnamed: U13.6, U20.4
unnamed: U13.7, U21.4
unnamed: U13.15, U14.4
PANEL_1: C39.1, J1.6, R27.1
PANEL_2: C41.1, J2.3, R29.1
PANEL_3: C43.1, J2.2, R31.1
READ_CURRENT: C27.1, J1.2, R17.1
READ_VOLTAGE: J1.5, TP16.2, TP17.2
RESET_PANEL_SWITCH: R6.1, U3.7, U3.15
REVERSE_BIAS: R7.1, U11.1, U12.1
RX: J1.3, J15.2
SCL: J1.9, J14.3, R39.1
SDA: J1.10, J14.4, R40.1
TX: J1.4, J15.3
~LADDER_RESET: R1.2, U13.10
